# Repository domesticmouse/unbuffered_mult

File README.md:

# Unbuffered Mult

An "unbuffered mult" is a passive signal splitter that splits one input signal into multiple outputs without using a powered buffer, like a TL074 op amp.
This means the signal can lose voltage or be slightly degraded with each signal tap, making it ideal for voltage non-critical signals like gates and triggers.
However, it is not recommended for voltage precise signals (CV), which require a buffered mult to maintain signal integrity.

**Note:** This is a learning exercise.

## Design intent

The intent of this design is to implement a 2hp wide EuroRack module.
The module will consist of two groups of four 3.5mm mono jacks.
There will be a common ground for the whole board. The first group of
four jacks will have their signal leads wired together, with their
switched terminal left floating.

The second group of four jacks will have their signal terminals wired together.
The first jack of the second group will have it's switched terminal connected
to the first group's signal wire.
This will normally connect the three output jacks into the first group if the
first socket of the second group is left unconnected.

If a cable is connected into the first socket of the second group, this will
disconnect the second group of sockets from the first group.

## Important dimensions

The width of the mainboard will be 9mm. The height of the board will be 110mm. The
thickness of the PCB will 1.6mm, the default thickness of a 2 layer PCB.

The faceplate dimensions are 2hp (9.8mm) wide, and 128.5 mm tall.

## Sources

- [fuzzySi](https://github.com/fuzzySi)'s [KiCad parts](https://github.com/fuzzySi/kicad)
- Wenzhou QingPu Electronics Co., Ltd's [WQP-WQP518MA](http://www.qingpu-electronics.com/en/products/WQP-PJ398SM-362.html)
- [DinkDonk](https://github.com/DinkDonk)'s [EDA 3D Model of the WQP-PJ398SM](https://github.com/elektrofon/eda-3d-models)
- [joem](https://github.com/joem)'s [Thonkiconn Breadboard Adapter V3](https://github.com/joem/thonkiconn_breadboard_adapter_v3)
- [thonk.co.uk](https://www.thonk.co.uk/)'s [Thonkiconn – 3.5mm Jack Sockets](https://www.thonk.co.uk/shop/thonkiconn/)
- [thonk.co.uk](https://www.thonk.co.uk/)'s [PJ398SM Datasheet](https://www.thonk.co.uk/wp-content/uploads/2018/07/Thonkiconn_Jack_Datasheet-new.jpg)
- [clacktronics](https://github.com/clacktronics) [AudioJacks](https://github.com/clacktronics/AudioJacks)
- [AI Synthesis](https://aisynthesis.com/)'s [AI001 Multiple](https://aisynthesis.com/product/multiple-eurorack-synthesizer-module/)
- [AI Synthesis](https://aisynthesis.com/)'s [AI001 Multiple Build Guide](https://aisynthesis.com/ai001-multiple-build-guide/)
- [Eurorack Panel Dimensions](https://www.exploding-shed.com/manuals-tutorials/manuals/standards-of-eurorack/eurorack-dimensions/) by [Exploding Shed](https://www.exploding-shed.com/)
- [EuroRack dimensions](https://midisoft.de/EuroRackDimensions/EuroRack_Dimensions.html)

## KiCanvas links

- [faceplate](https://kicanvas.org/?github=https%3A%2F%2Fgithub.com%2Fdomesticmouse%2Funbuffered_mult%2Fblob%2Fmain%2Fhardware%2Ffaceplate%2Ffaceplate.kicad_pro)
- [mainboard](https://kicanvas.org/?github=https%3A%2F%2Fgithub.com%2Fdomesticmouse%2Funbuffered_mult%2Fblob%2Fmain%2Fhardware%2Fmainboard%2Fmainboard.kicad_pro)

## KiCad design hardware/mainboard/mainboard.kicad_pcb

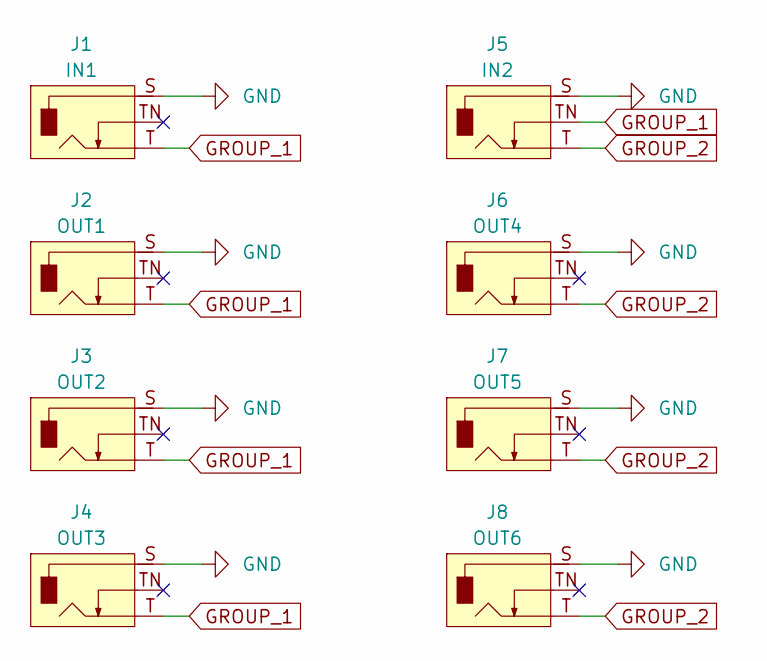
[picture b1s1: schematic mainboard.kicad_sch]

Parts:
J1: IN1; Jack_3.5mm_WQP-PJ398SM_Vertical_Tight
J2: OUT1; Jack_3.5mm_WQP-PJ398SM_Vertical_Tight
J3: OUT2; Jack_3.5mm_WQP-PJ398SM_Vertical_Tight
J4: OUT3; Jack_3.5mm_WQP-PJ398SM_Vertical_Tight
J5: IN2; Jack_3.5mm_WQP-PJ398SM_Vertical_Tight
J6: OUT4; Jack_3.5mm_WQP-PJ398SM_Vertical_Tight
J7: OUT5; Jack_3.5mm_WQP-PJ398SM_Vertical_Tight
J8: OUT6; Jack_3.5mm_WQP-PJ398SM_Vertical_Tight

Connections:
GND: J1.S, J2.S, J3.S, J4.S, J5.S, J6.S, J7.S, J8.S
GROUP_1: J1.T, J2.T, J3.T, J4.T, J5.TN
GROUP_2: J5.T, J6.T, J7.T, J8.T

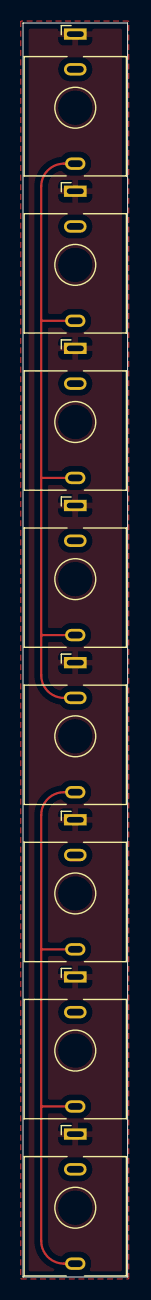
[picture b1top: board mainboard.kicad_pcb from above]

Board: 2 copper layers, 9.2 x 110.3 mm, 8 parts (0 on the bottom side), 3 nets.

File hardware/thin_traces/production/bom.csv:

Designator,Footprint,Quantity,Value,LCSC Part #
J1,Jack_3.5mm_WQP-PJ398SM_Vertical_Tight,1,IN1,
J2,Jack_3.5mm_WQP-PJ398SM_Vertical_Tight,1,OUT1,
J3,Jack_3.5mm_WQP-PJ398SM_Vertical_Tight,1,OUT2,
J4,Jack_3.5mm_WQP-PJ398SM_Vertical_Tight,1,OUT3,
J5,Jack_3.5mm_WQP-PJ398SM_Vertical_Tight,1,IN2,
J6,Jack_3.5mm_WQP-PJ398SM_Vertical_Tight,1,OUT4,
J7,Jack_3.5mm_WQP-PJ398SM_Vertical_Tight,1,OUT5,
J8,Jack_3.5mm_WQP-PJ398SM_Vertical_Tight,1,OUT6,

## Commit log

2025-11-12 License, sources
2025-11-12 More sources
2025-11-12 More detail
2025-11-13 Add the boards
2025-11-13 Revise board dimensions and socket specifications
    Updated dimensions and specifications for the mainboard and faceplate.
2025-11-14 Clean up
2025-11-14 Add dimensions
2025-11-14 Useful dimensions document
2025-11-20 Drop thin_traces
2025-11-20 Update mainboard
2025-11-20 New faceplate
2025-11-20 Init gemini
2025-11-20 Updated faceplate
2025-11-20 Send it
2025-11-20 Add KiCanvas links
2025-12-01 Re-print
